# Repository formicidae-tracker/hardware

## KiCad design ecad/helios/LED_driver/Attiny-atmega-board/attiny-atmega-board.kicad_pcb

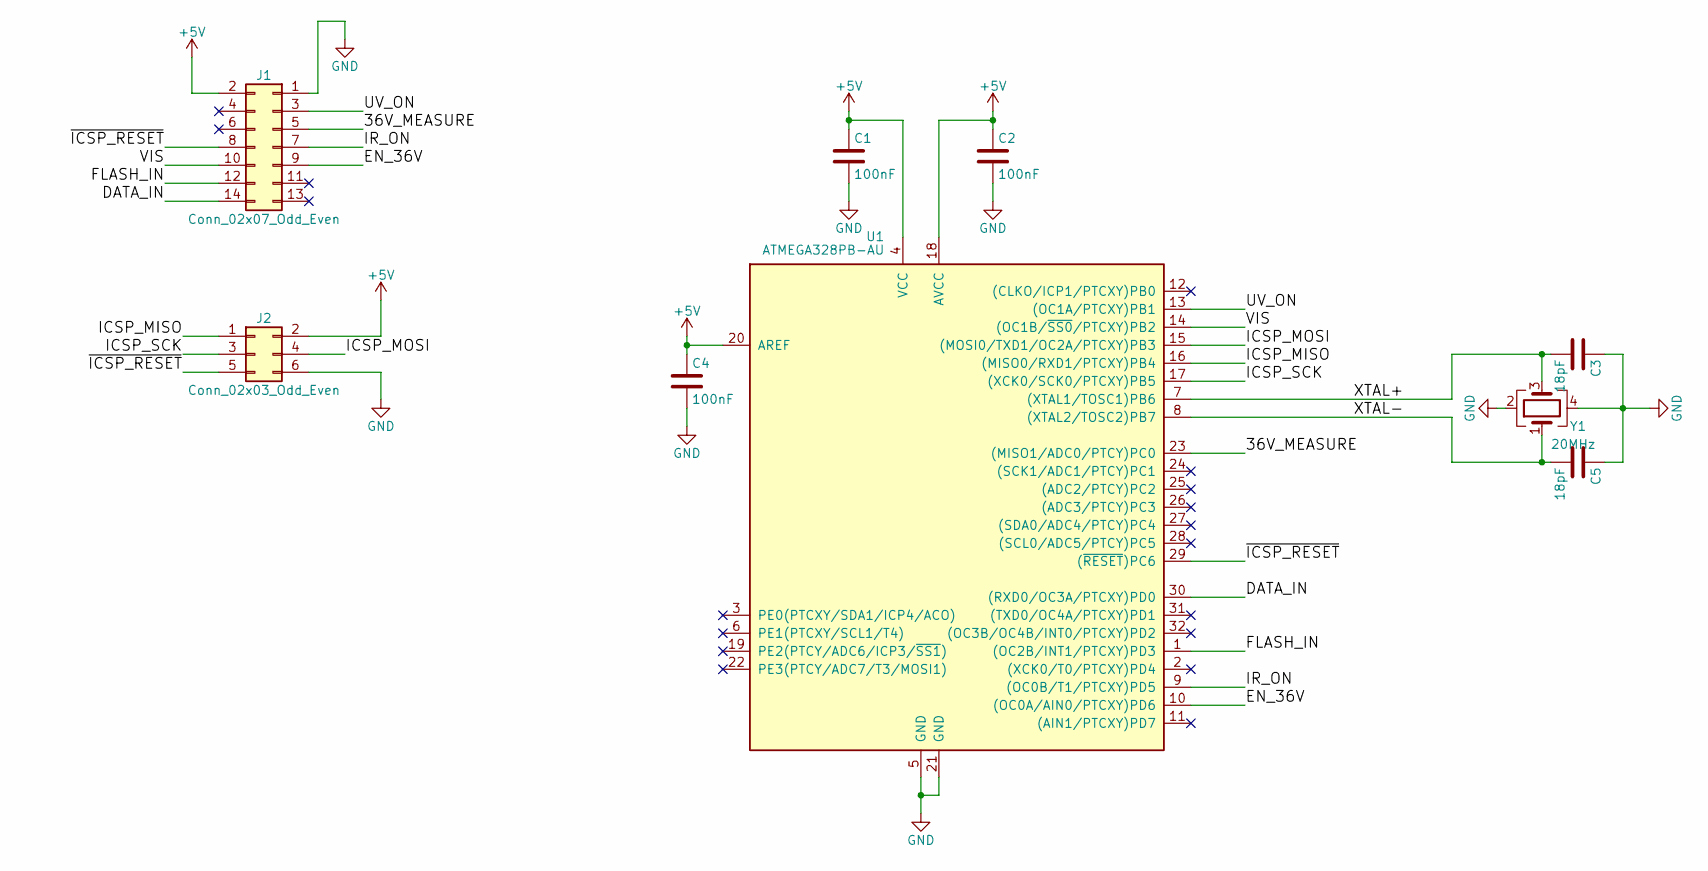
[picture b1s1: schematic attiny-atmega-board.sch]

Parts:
C1, C2, C4: 100nF; C_0603_HandSoldering
C3, C5: 18pF; C_0603_HandSoldering
J1: Conn_02x07_Odd_Even; Pin_Header_Straight_2x07_Pitch1.27mm
J2: Conn_02x03_Odd_Even; Pin_Header_Straight_2x03_Pitch2.54mm_SMD
U1: ATMEGA328PB-AU; TQFP-32_7x7mm_Pitch0.8mm
Y1: 20MHz; Crystal_SMD_Abracon_ABM8G-4pin_3.2x2.5mm; Part Number ABM8G-20.000MHZ-18-D2Y-T

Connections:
+5V: C1.1, C2.1, C4.1, J1.2, J2.2, U1.4 (VCC), U1.18 (AVCC), U1.20 (AREF)
/36V_MEASURE: J1.5, U1.23 ((MISO1/ADC0/PTCY)PC0)
/DATA_IN: J1.14, U1.30 ((RXD0/OC3A/PTCXY)PD0)
/EN_36V: J1.9, U1.10 ((OC0A/AIN0/PTCXY)PD6)
/FLASH_IN: J1.12, U1.1 ((OC2B/INT1/PTCXY)PD3)
/ICSP_MISO: J2.1, U1.16 ((MISO0/RXD1/PTCXY)PB4)
/ICSP_MOSI: J2.4, U1.15 ((MOSI0/TXD1/OC2A/PTCXY)PB3)
/ICSP_SCK: J2.3, U1.17 ((XCK0/SCK0/PTCXY)PB5)
/IR_ON: J1.7, U1.9 ((OC0B/T1/PTCXY)PD5)
/UV_ON: J1.3, U1.13 ((OC1A/PTCXY)PB1)
/VIS: J1.10, U1.14 ((OC1B/~SS0~/PTCXY)PB2)
/XTAL+: C3.2, U1.7 ((XTAL1/TOSC1)PB6), Y1.3
/XTAL-: C5.2, U1.8 ((XTAL2/TOSC2)PB7), Y1.1
/~ICSP_RESET: J1.8, J2.5, U1.29 ((~RESET~)PC6)
GND: C1.2, C2.2, C3.1, C4.2, C5.1, J1.1, J2.6, U1.5 (GND), U1.21 (GND), Y1.2, Y1.4

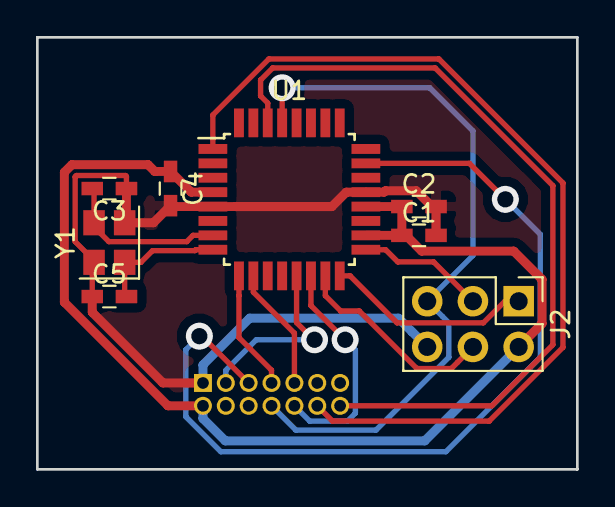
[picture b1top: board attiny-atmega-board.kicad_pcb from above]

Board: 2 copper layers, 30.0 x 24.0 mm, 9 parts (1 on the bottom side), 15 nets.

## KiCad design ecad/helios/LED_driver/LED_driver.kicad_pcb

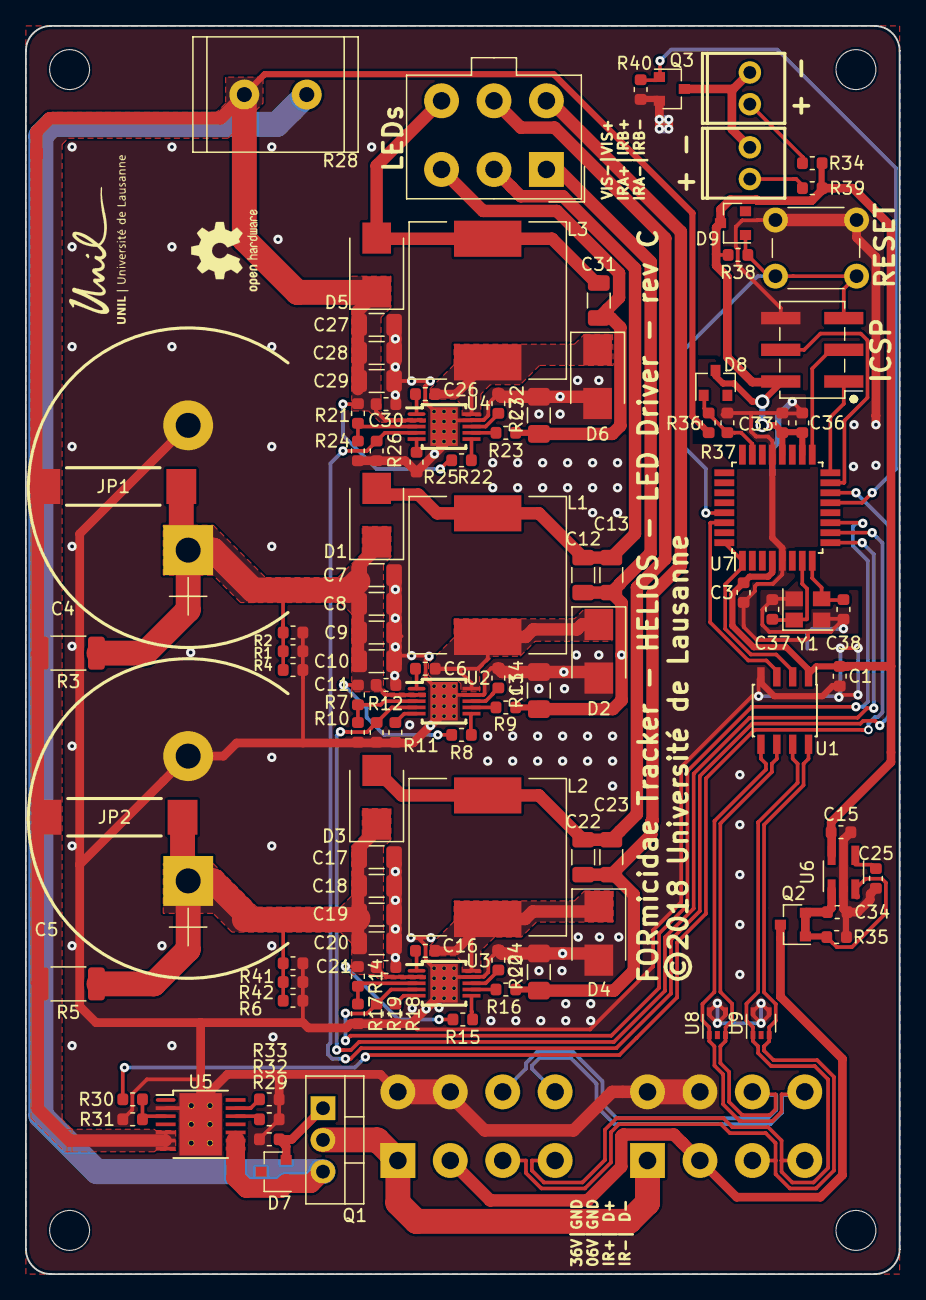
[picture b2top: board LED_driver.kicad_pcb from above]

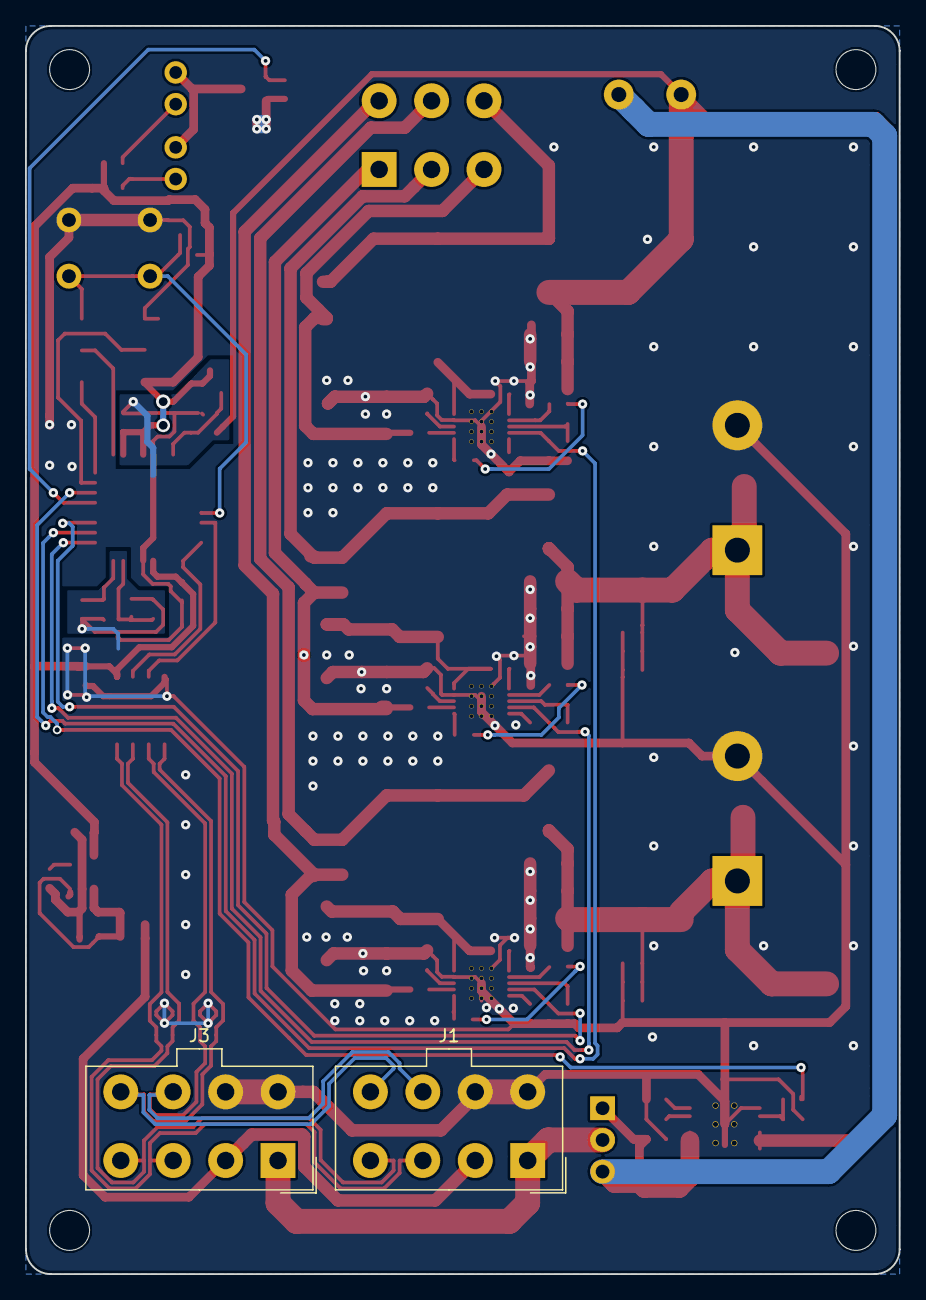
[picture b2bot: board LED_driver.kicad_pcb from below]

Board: 2 copper layers, 70.0 x 100.0 mm, 112 parts (2 on the bottom side), 62 nets.

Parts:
C1, C3, C6, C14, C16, C24, C26, C32, C33, C36: 100nF; C_0603_1608Metric
C4, C5: 4.7mF; CP_Radial_D25.0mm_P10.00mm_SnapIn
C7, C8, C9, C10, C12, C13, C17, C18, C19, C20, C22, C23, C27, C28, C29, C31: 4.7uF,50V; C_1206_3216Metric
C11, C21, C25, C30: 10nF, 50V; C_0603_1608Metric
C15, C34: 1uF; C_0603_1608Metric
C37, C38: 18pF; C_0603_1608Metric
D1, D2, D3, D4, D5, D6: 60V, 2A; D_SMB
D7: 10V; D_SOT-23_KAN
D8, D9: BAT54; D_SOT-23_ANK
J1, J3: 5566-08A2; Molex_MiniFit-JR-5556-08A_2x04x4.20mm_Straight
J2: 5566-06A2; Molex_MiniFit-JR-5556-06A_2x03x4.20mm_Straight
J4: .100 2row header; PinHeader_2x03_P2.54mm_Vertical_SMD
J5, J6: LED HDR; 640454-2
JP1, JP2: S1621-46R
L1, L2, L3: 100uH, 2.5A; 7447709101
Q1: IRF9Z34NPbF; TO-220-3_Vertical
Q2: PMV48XP,215; SOT-23
Q3: BSS138L; SOT-23
R1, R2, R4, R6, R41, R42: 100k; R_0603_1608Metric
R3, R5: 4.7, 3/4W; R_2010_5025Metric
R7, R14, R21: 1.96M; R_0603_1608Metric
R8, R15, R22: 10M; R_0603_1608Metric
R9, R16, R23: 1K; R_0603_1608Metric
R10, R17, R24: 66.5k; R_0603_1608Metric
R11, R18: 267k; R_0603_1608Metric
R12, R19, R26, R29, R31, R32, R35, R36, R40: 100K; R_0603_1608Metric
R13, R20: 0.2, 1%, 0.5W; R_1206_3216Metric_Pad1.42x1.75mm_HandSolder
R25: 162k; R_0603_1608Metric
R27: 3.3, 1%, 0.5W; R_1206_3216Metric_Pad1.42x1.75mm_HandSolder
R28: 47, 5W; R_Radial_Power_L13.0mm_W9.0mm_P5.00mm
R30, R38: 10K; R_0603_1608Metric
R33: 2.94K; R_0603_1608Metric
R34, R39: 82; R_0603_1608Metric
R37: 12.7k; R_0603_1608Metric
SW1: SW_Push; SW_PUSH_6mm
U1: UA9637; SOIC-8_3.9x4.9mm_P1.27mm
U2, U3, U4: TPS92512; PDSO-10-1EP-3x3mm-Pitch0.5mm
U5: TPS1H100AQPWPRQ1; HTSSOP-14-1EP_4.4x6.5mm_Pitch0.65mm_ThermalPad
U6: LP3985IM5-5.0/NOPB; SOT-23-5_HandSoldering
U7: ATMEGA328PB-AU; TQFP-32_7x7mm_P0.8mm
U8, U9: SP1002-02JTG; SOT-353_SC-70-5
Y1: 20MHz; Crystal_SMD_Abracon_ABM8G-4Pin_3.2x2.5mm

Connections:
+5V: C1.2, C3.1, C15.1, C33.1, C36.1, D8.1, D9.1, J4.2, R34.2, R38.1, R39.2, U1.1, U6.5, U7.4, U7.18, U7.20
+36V: C27.1, C28.1, C29.1, C30.1, D5.1, JP1.2, JP2.2, R3.2, R5.2, R21.1, R22.2, R28.2, R36.1, U4.2, U5.5, U5.6, U5.7
/Controller/FLASH_IN: U1.2, U7.1, U7.32
/Controller/ICSP_MISO: J4.1, U7.16
/Controller/ICSP_MOSI: J4.4, U7.15
/Controller/ICSP_SCK: J4.3, U7.17
/Controller/IR_A_ON: R12.1, U2.4, U7.9
/Controller/IR_B_ON: R19.1, U3.4, U7.11
/Controller/UV_ON: Q3.1, R40.1, U7.13
/Controller/V36_MEASURE: D8.2, R36.2, R37.1, U7.23
/Controller/XTAL+: C37.2, U7.7, Y1.1
/Controller/XTAL-: C38.2, U7.8, Y1.3
/Controller/~ICSP_RESET: D9.2, J4.5, R38.2, SW1.2, U7.29
/DATA_+: J1.7, J3.7, U1.6, U8.3
/DATA_-: J1.8, J3.8, U1.5, U8.1
/IRA+: C12.1, C13.1, D1.2, J2.2, L1.2
/IRA-: C12.2, C13.2, J2.1, R9.1, R13.1
/IRB+: C22.1, C23.1, D3.2, J2.5, L2.2
/IRB-: C22.2, C23.2, J2.4, R16.1, R20.1
/LED Drivers/Buck Current Regulator 1.5A 1/PHI: C6.1, D2.1, L1.1, U2.10
/LED Drivers/Buck Current Regulator 1.5A 1/VIN: C4.1, C7.1, C8.1, C9.1, C10.1, C11.1, D1.1, JP1.1, R1.1, R2.1, R3.1, R4.1, R7.1, R8.2, U2.2
/LED Drivers/Buck Current Regulator 1.5A 2/PHI: C16.1, D4.1, L2.1, U3.10
/LED Drivers/Buck Current Regulator 1.5A 2/VIN: C5.1, C17.1, C18.1, C19.1, C20.1, C21.1, D3.1, JP2.1, R5.1, R6.1, R14.1, R15.2, R41.1, R42.1, U3.2
/LED Drivers/Buck Current Regulator 1A/PHI: C26.1, D6.1, L3.1, U4.10
/LED Drivers/VIS_ON: R26.1, U4.4, U7.14
/Power_Management/EN36: R30.2, U7.10
/Power_Management/V6_PROTECTED: C34.1, Q2.1, Q2.2, R35.1, U6.1, U6.3
/Power_Management/V36_PROTECTED: D7.1, Q1.3, R28.1, U5.8, U5.9, U5.10
/Receivers/DATA: U1.3, U7.30
/TRIG_+: J1.3, J3.3, U1.8, U9.3
/TRIG_-: J1.4, J3.4, U1.7, U9.1
/VIS+: C31.1, D5.2, J2.6, L3.2
/VIS-: C31.2, J2.3, R23.1, R27.1
/VS6: J1.2, J3.2, Q2.3
/VS36: J1.1, J3.1, Q1.2
GND: C1.1, C3.2, C4.2, C5.2, C7.2, C8.2, C9.2, C10.2, C11.2, C14.2, C15.2, C17.2, C18.2, C19.2, C20.2, C21.2, C24.2, C25.2, C27.2, C28.2, C29.2, C30.2, C32.2, C33.2, C34.2, C36.2, C37.1, C38.1, D2.2, D4.2, D6.2, J1.5, J1.6, J3.5, J3.6, J4.6, Q3.2, R1.2, R2.2, R4.2, R6.2, R10.2, R11.2, R12.2, R13.2, R17.2, R18.2, R19.2, R20.2, R24.2, R25.2, R26.2, R27.2, R29.2, R31.2, R32.2, R33.2, R35.2, R37.2, R40.2, R41.2, R42.2, SW1.1, U1.4, U2.9, U2.11, U3.9, U3.11, U4.9, U4.11, U5.2, U5.15, U6.2, U7.5, U7.21, U8.4, U8.5, U9.4, U9.5, Y1.2, Y1.4
unnamed: C6.2, U2.1
unnamed: C14.1, U2.8
unnamed: C16.2, U3.1
unnamed: C24.1, U3.8
unnamed: C25.1, U6.4
unnamed: C26.2, U4.1
unnamed: C32.1, U4.8
unnamed: D7.2, Q1.1, R29.1
unnamed: J5.1, R34.1
unnamed: J5.2, J6.2, Q3.3
unnamed: J6.1, R39.1
unnamed: R8.1, U2.6
unnamed: R9.2, U2.7
unnamed: R7.2, R10.1, U2.3
unnamed: R11.1, U2.5
unnamed: R14.2, R17.1, U3.3
unnamed: R15.1, U3.6
unnamed: R16.2, U3.7
unnamed: R18.1, U3.5
unnamed: R21.2, R24.1, U4.3
unnamed: R22.1, U4.6
unnamed: R23.2, U4.7
unnamed: R25.1, U4.5
unnamed: R30.1, R31.1, U5.3
unnamed: R32.1, U5.12
unnamed: R33.1, U5.13

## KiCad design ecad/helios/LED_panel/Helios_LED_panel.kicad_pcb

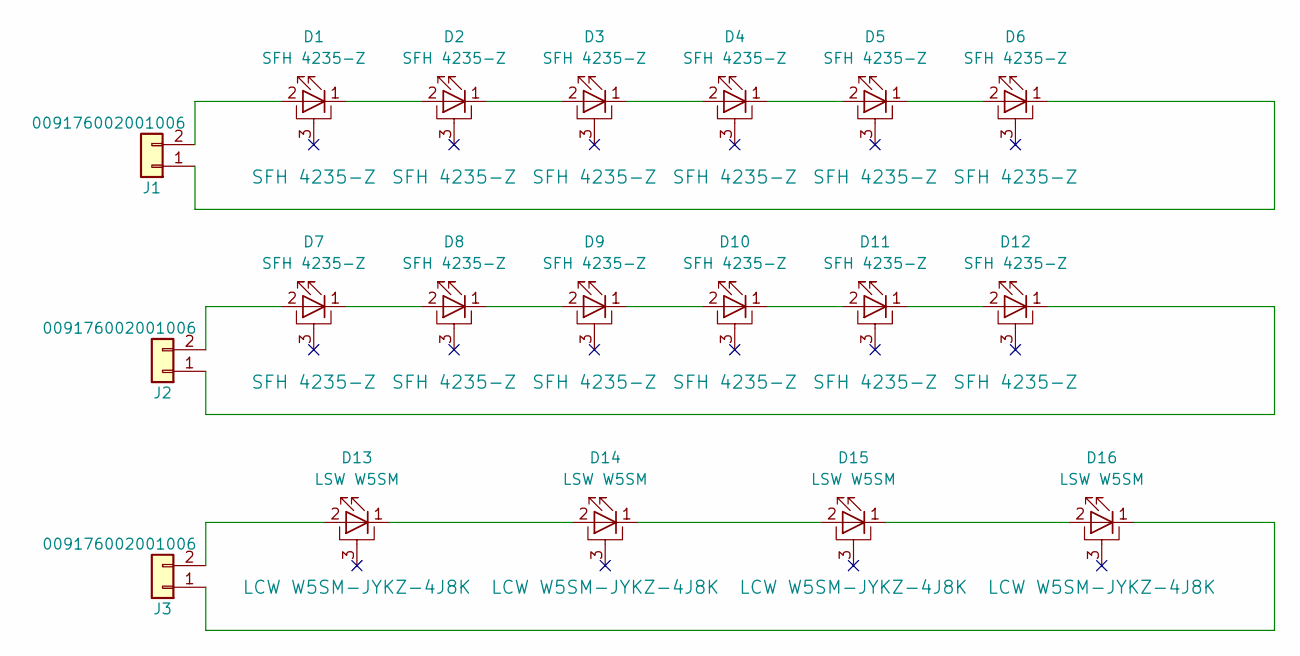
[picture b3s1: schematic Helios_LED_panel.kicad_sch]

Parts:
D1, D2, D3, D4, D5, D6, D7, D8, D9, D10, D11, D12: SFH 4235-Z; OSRAM_Platinium_Dragon
D13, D14, D15, D16: LSW W5SM; OSRAM_Platinium_Dragon
J1, J2, J3: 009176002001006; 009176002701106

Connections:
unnamed: D1.1 (K), D2.2 (A)
unnamed: D1.2 (A), J1.2
unnamed: D2.1 (K), D3.2 (A)
unnamed: D3.1 (K), D4.2 (A)
unnamed: D4.1 (K), D5.2 (A)
unnamed: D5.1 (K), D6.2 (A)
unnamed: D6.1 (K), J1.1
unnamed: D7.1 (K), D8.2 (A)
unnamed: D7.2 (A), J2.2
unnamed: D8.1 (K), D9.2 (A)
unnamed: D10.1 (K), D11.2 (A)
unnamed: D9.1 (K), D10.2 (A)
unnamed: D11.1 (K), D12.2 (A)
unnamed: D12.1 (K), J2.1
unnamed: D13.1 (K), D14.2 (A)
unnamed: D13.2 (A), J3.2
unnamed: D14.1 (K), D15.2 (A)
unnamed: D15.1 (K), D16.2 (A)
unnamed: D16.1 (K), J3.1

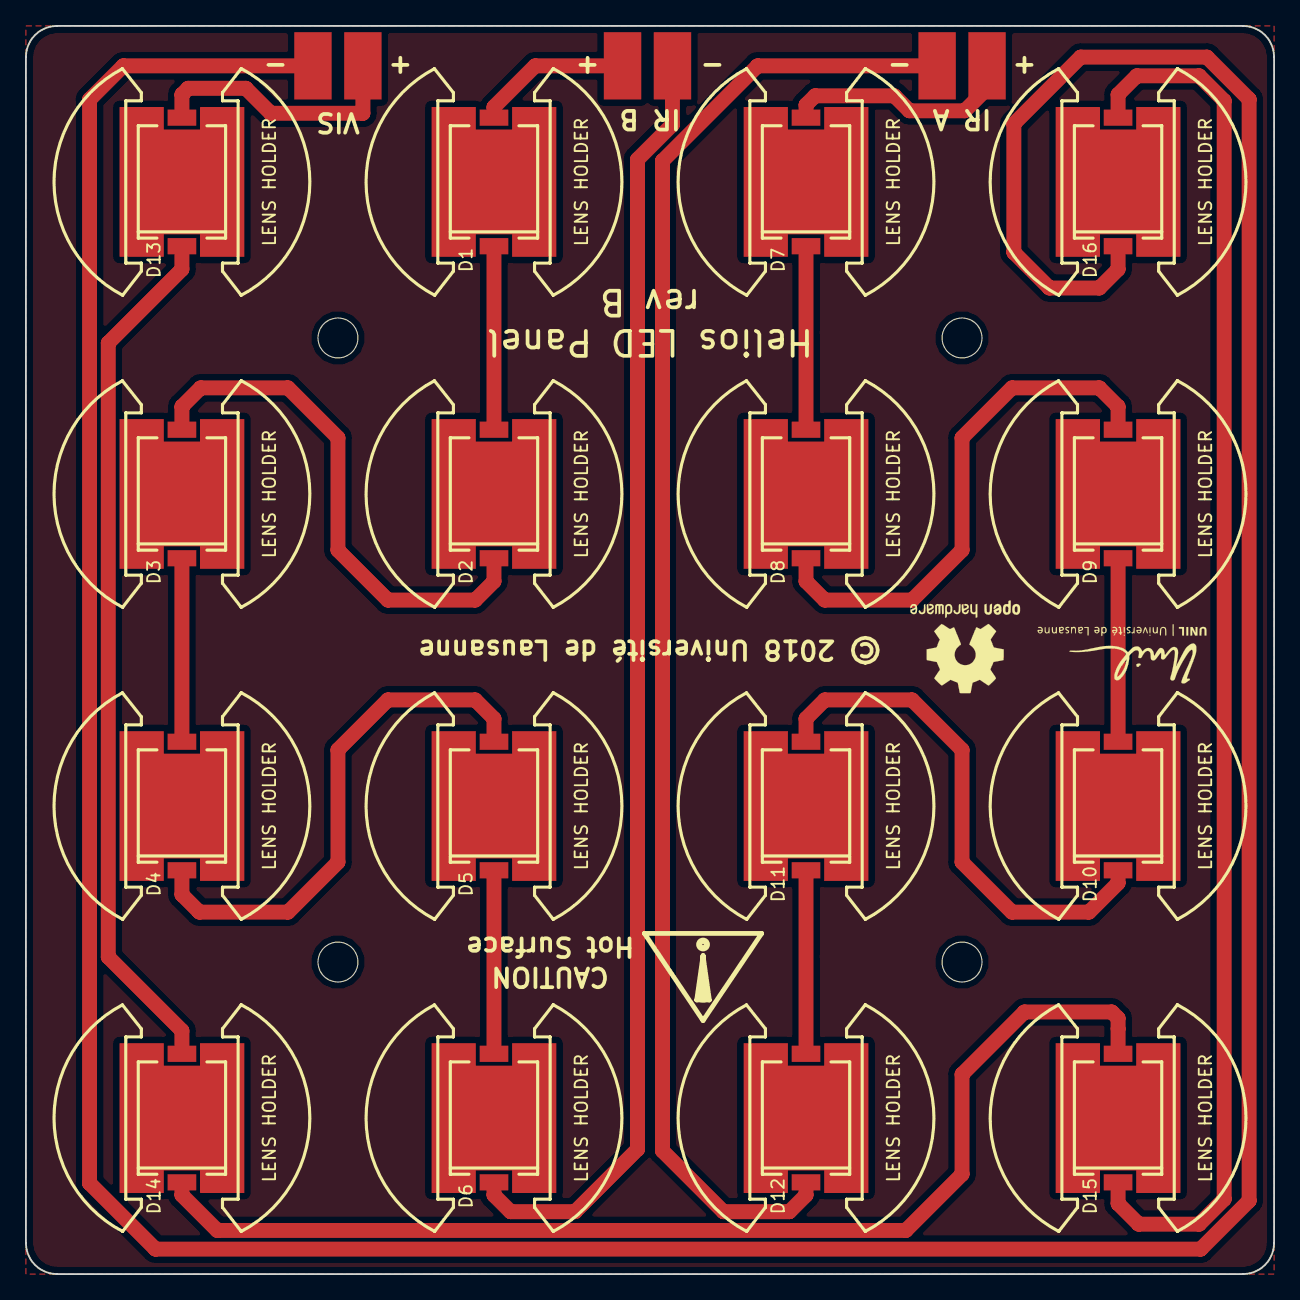
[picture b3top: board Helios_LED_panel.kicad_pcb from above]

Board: 2 copper layers, 100.0 x 100.0 mm, 19 parts (0 on the bottom side), 19 nets.

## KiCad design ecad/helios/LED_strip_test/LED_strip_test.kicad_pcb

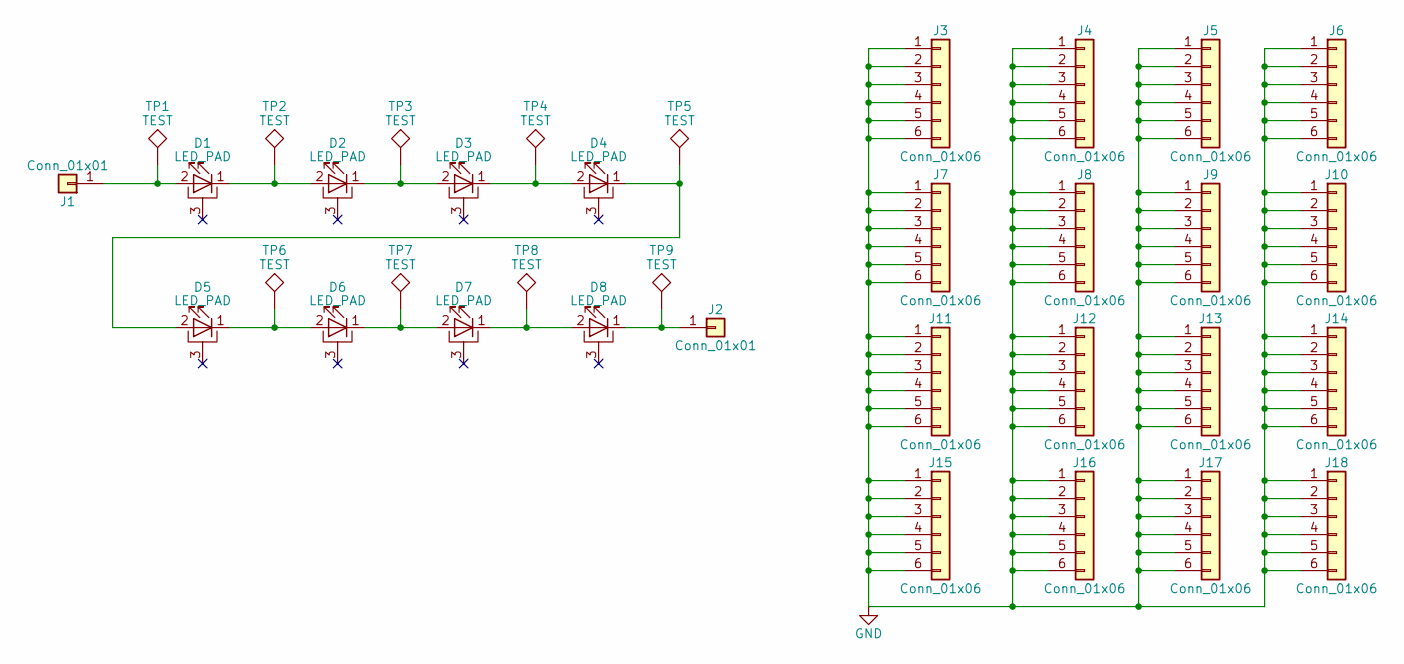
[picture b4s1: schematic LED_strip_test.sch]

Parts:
D1, D2, D3, D4, D5, D6, D7, D8: LED_PAD; OSRAM_Platinium_Dragon
J1, J2: Conn_01x01; SolderWirePad_single_1-5mmDrill
J3, J4, J5, J6, J7, J8, J9, J10, J11, J12, J13, J14, J15, J16, J17, J18: Conn_01x06; Pin_Header_Straight_1x06_Pitch2.54mm_Centered
TP1, TP2, TP3, TP4, TP5, TP6, TP7, TP8, TP9: TEST; SolderWirePad_single_1-5mmDrill

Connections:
GND: J3.1, J3.2, J3.3, J3.4, J3.5, J3.6, J4.1, J4.2, J4.3, J4.4, J4.5, J4.6, J5.1, J5.2, J5.3, J5.4, J5.5, J5.6, J6.1, J6.2, J6.3, J6.4, J6.5, J6.6, J7.1, J7.2, J7.3, J7.4, J7.5, J7.6, J8.1, J8.2, J8.3, J8.4, J8.5, J8.6, J9.1, J9.2, J9.3, J9.4, J9.5, J9.6, J10.1, J10.2, J10.3, J10.4, J10.5, J10.6, J11.1, J11.2, J11.3, J11.4, J11.5, J11.6, J12.1, J12.2, J12.3, J12.4, J12.5, J12.6, J13.1, J13.2, J13.3, J13.4, J13.5, J13.6, J14.1, J14.2, J14.3, J14.4, J14.5, J14.6, J15.1, J15.2, J15.3, J15.4, J15.5, J15.6, J16.1, J16.2, J16.3, J16.4, J16.5, J16.6, J17.1, J17.2, J17.3, J17.4, J17.5, J17.6, J18.1, J18.2, J18.3, J18.4, J18.5, J18.6
unnamed: D1.1 (K), D2.2 (A), TP2.1
unnamed: D1.2 (A), J1.1, TP1.1
unnamed: D2.1 (K), D3.2 (A), TP3.1
unnamed: D3.1 (K), D4.2 (A), TP4.1
unnamed: D4.1 (K), D5.2 (A), TP5.1
unnamed: D5.1 (K), D6.2 (A), TP6.1
unnamed: D6.1 (K), D7.2 (A), TP7.1
unnamed: D7.1 (K), D8.2 (A), TP8.1
unnamed: D8.1 (K), J2.1, TP9.1

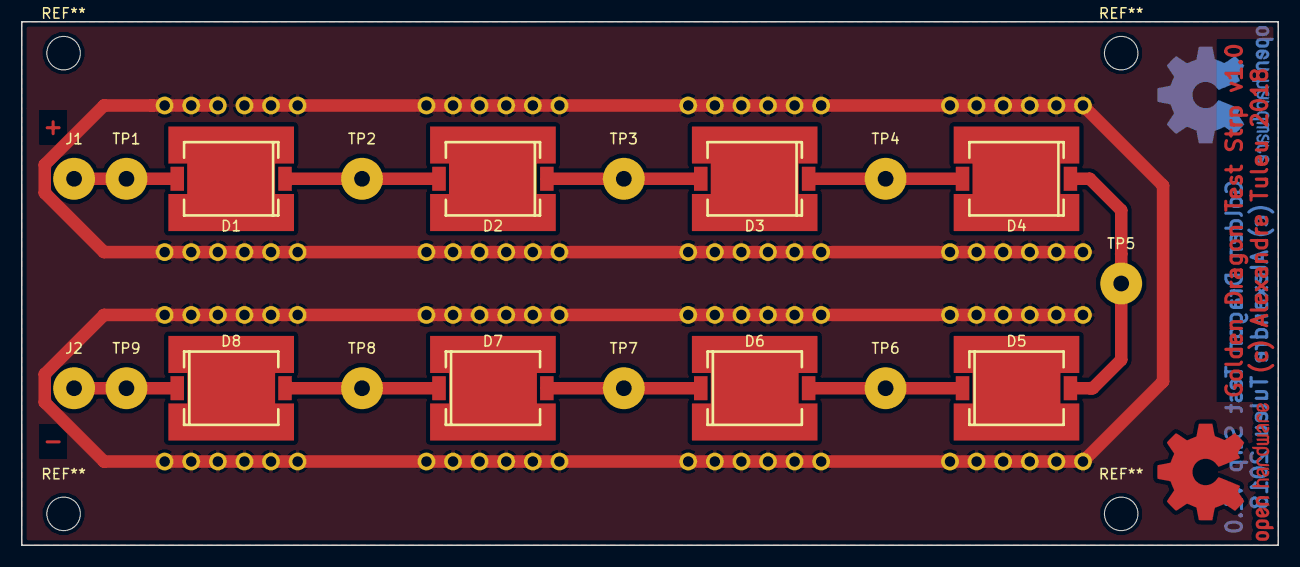
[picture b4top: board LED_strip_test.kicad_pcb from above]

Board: 2 copper layers, 120.0 x 50.0 mm, 35 parts (0 on the bottom side), 10 nets.

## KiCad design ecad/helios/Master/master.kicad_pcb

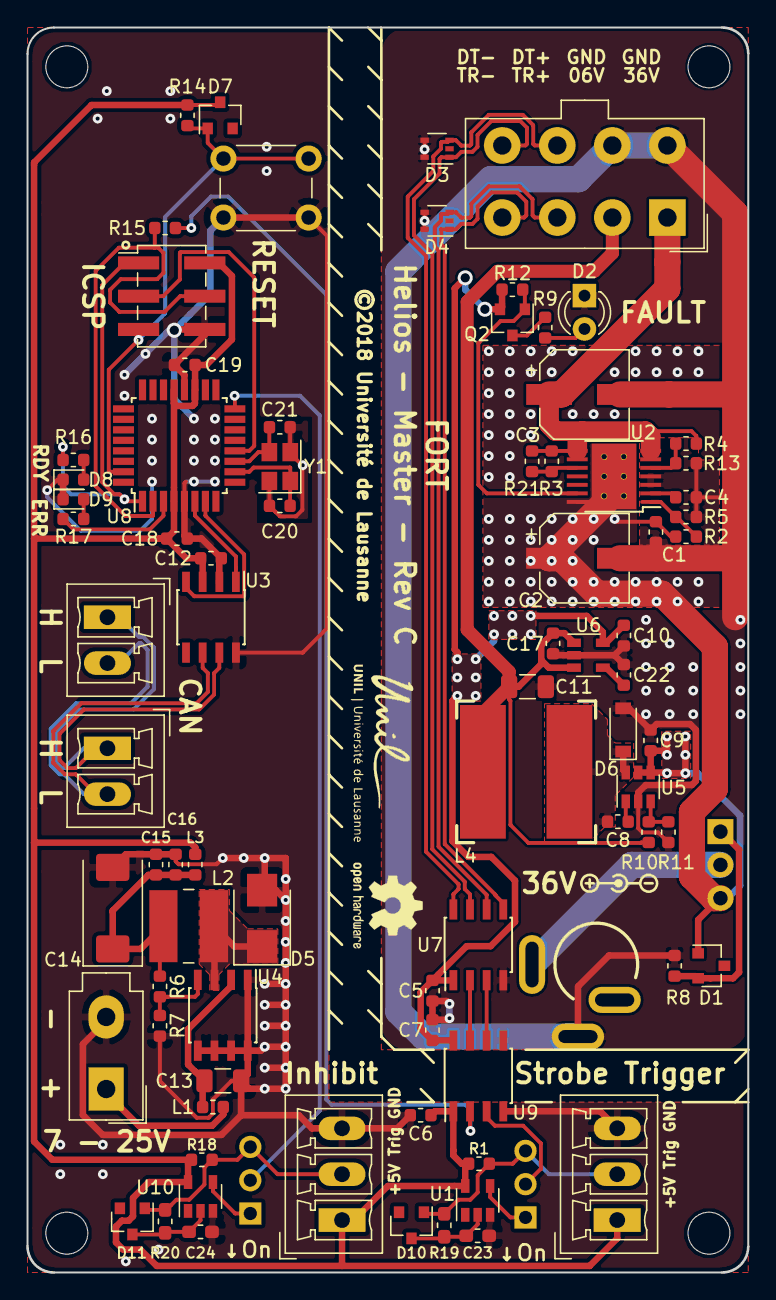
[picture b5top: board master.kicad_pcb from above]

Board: 2 copper layers, 55.0 x 95.0 mm, 88 parts (1 on the bottom side), 53 nets.

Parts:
C1, C5, C6, C7, C12, C16, C18, C19: 100n; C_0603_1608Metric
C2, C3: 47uF; CP_Elec_6.3x7.7
C4, C22: 10nF, 50V; C_0603_1608Metric
C8: 0.22uF, 25V; C_0603_1608Metric
C9, C10, C17: 1uF, 50V; C_0603_1608Metric
C11: 47uF, 10V; C_1206_3216Metric
C13: 22uF, 25V; C_1206_3216Metric
C14: 470u, 6.3V; CP_EIA-7343-31_Kemet-D
C15: 4u7, 6.3V; C_0603_1608Metric
C20, C21: 18pF; C_0603_1608Metric
C23, C24: 1nF; C_0603_1608Metric_Pad1.05x0.95mm_HandSolder
D1: 10V; D_SOT-23_KAN
D2: RED; LED_D3.0mm
D3, D4: SP1002-02TG; SOT-353_SC-70-5
D5: B260, 60V, 2A; D_SMB
D6: 60V, 1A; D_SOD-123
D7, D10, D11: BAT54; D_SOT-23_ANK
D8: GREEN; LED_0603_1608Metric
D9: YELLOW; LED_0603_1608Metric
J1: 5566-02A; Molex_Mini-Fit_Jr_5566-02A_2x01_P4.20mm_Vertical
J2, J3: MCV 1,5/ 2-G-3,5; PhoenixContact_MCV_1,5_2-G-3.5_1x02_P3.50mm_Vertical
J4, J8: MCV 1,5/ 3-G-3,5; PhoenixContact_MCV_1,5_3-G-3.5_1x03_P3.50mm_Vertical
J5: PJ-032A
J6: MiniFit JR 5566 08A2; Molex_MiniFit-JR-5556-08A_2x04x4.20mm_Straight
J7: M20-8760342; PinHeader_2x03_P2.54mm_Vertical_SMD
JP1, JP2: .100 Header; PinHeader_1x03_P2.54mm_Vertical
L1, L3: 500mA Fuse; R_0603_1608Metric
L2: 68uH, 560mA; L_Wuerth_WE-PD2-Typ-MS
L4: 100uH, 0.7A; SRN1060-XXXM
MH1, MH2, MH3, MH4: M3; MountingHole_3.2mm_M3_DIN965
Q1: IRF9Z34NPbF; TO-220-3_Horizontal_TabDown
Q2: BSS84P; SOT-23
R1, R5, R13, R14, R18: 10K; R_0603_1608Metric
R2: 270k; R_0603_1608Metric
R3, R21: 51; R_0603_1608Metric
R4: 390k; R_0603_1608Metric
R6: 15k; R_0603_1608Metric
R7: 4k87; R_0603_1608Metric
R8, R12: 100K; R_0603_1608Metric
R9, R11, R16, R17: 1k; R_0603_1608Metric
R10: 6.98K; R_0603_1608Metric
R15: 1K; R_0603_1608Metric
R19, R20: 10K; R_0603_1608Metric_Pad1.05x0.95mm_HandSolder
SW1: 1825910-6; SW_PUSH_6mm
U1, U10: 74LVC1G17; SOT-23-5
U2: STEF01FTR; HTSSOP-14-1EP_4.4x6.5mm_Pitch0.65mm_ThermalPad
U3: MCP2561-E/SN; SOIC-8_3.9x4.9mm_P1.27mm
U4: MIC4680YM; SOIC-8_3.9x4.9mm_P1.27mm
U5: LM2842Y; SOT-23-6
U6: LP3985IM5-5.0/NOPB; SOT-23-5
U7: UA9638; SOIC-8_3.9x4.9mm_P1.27mm
U8: ATMEGA16M1-AU; TQFP-32_7x7mm_P0.8mm
U9: ISO7320FC; SOIC-8_3.9x4.9mm_P1.27mm
Y1: 16MHz; Crystal_SMD_SeikoEpson_FA238-4Pin_3.2x2.5mm

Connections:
+5V: C6.1, C12.1, C18.1, C19.1, D7.1, J4.1, J7.2, J8.1, L3.1, R1.1, R14.1, R18.1, U1.5, U3.3, U8.4, U8.19, U8.21, U9.1, U10.5
+12V: J1.1, L1.2
/12V to 5V LDO/5V_UNPROTECTED: C14.1, C15.1, C16.1, L2.2, L3.2, R6.1
/12V to 5V LDO/FB: R6.2, R7.1, U4.4
/12V to 5V LDO/SW: D5.1, L2.1, U4.3
/12V to 5V LDO/VIN_PROTECTED: C13.1, L1.1, U4.2
/CAN Transceiver/CAN+: J2.1, J3.1, U3.7
/CAN Transceiver/CAN-: J2.2, J3.2, U3.6
/Filter 1/FILTERED: JP1.1, U1.4
/Filter 1/IN: D10.2, J4.2, JP1.3, R1.2, R19.2
/Filter 1/SMOOTHED: C23.1, D10.1, R19.1, U1.2
/Filter 2/FILTERED: JP2.1, U10.4
/Filter 2/IN: D11.2, J8.2, JP2.3, R18.2, R20.2
/Filter 2/SMOOTHED: C24.1, D11.1, R20.1, U10.2
/INHIBIT: JP2.2, U8.16
/Output/6V_Regulator/BOOT: C8.1, U5.1
/Output/6V_Regulator/BYPASS: C22.1, U6.4
/Output/6V_Regulator/FB: R10.2, R11.1, U5.3
/Output/6V_Regulator/SW: C8.2, D6.1, L4.1, U5.6
/Output/DATA: R15.1, U9.2
/Output/DATA_+: D3.3, J6.7, U7.8
/Output/DATA_-: D3.1, J6.8, U7.7
/Output/DATA_ISO: U7.2, U9.7
/Output/GNDSUPPLY: C1.2, C2.2, C3.2, C4.2, C5.2, C7.2, C9.2, C10.2, C11.2, C17.2, C22.2, D2.1, D3.4, D3.5, D4.4, D4.5, D6.2, J5.2, J6.5, J6.6, R5.2, R8.2, R11.2, R13.2, U2.3, U2.4, U5.2, U6.2, U7.4, U9.5
/Output/ILIM: R3.2, R21.2, U2.10
/Output/IR_ON+: D4.3, J6.3, U7.6
/Output/IR_ON-: D4.1, J6.4, U7.5
/Output/LED_LIM: D2.2, R9.2
/Output/LED_ON: Q2.3, R9.1
/Output/PG: Q2.1, R12.2, U2.13
/Output/REV_ON: D1.2, Q1.1, R8.1
/Output/TRIGGER_ISO: U7.3, U9.6
/Output/UVLO: R2.2, R5.1, U2.1
/Output/V5: C5.1, C7.1, C10.1, Q2.2, R12.1, U6.5, U7.1, U9.8
/Output/V6: C11.1, C17.1, J6.2, L4.2, R10.1, U6.1, U6.3
/Output/V36: C3.1, J6.1, R3.1, R4.1, R21.1, U2.6, U2.7, U2.8, U2.9
/Output/VCLAMP: R4.2, R13.1, U2.5
/Output/VSUPPLY: J5.1, Q1.2
/Output/V_PROTECTED: C1.1, C2.1, C9.1, D1.1, Q1.3, R2.1, U2.14, U2.15, U5.4, U5.5
/Output/dVdt: C4.1, U2.2
/TRIGGER: JP1.2, U9.3
/UC/ICSP_MISO: J7.1, R16.1, U8.1
/UC/ICSP_MOSI: J7.4, R15.2, U8.2
/UC/ICSP_SCK: J7.3, U8.12
/UC/LED_ERROR: R17.1, U8.3
/UC/RXCAN: U3.4, U8.7
/UC/TXCAN: U3.1, U8.6
/UC/XTAL1: C20.2, U8.10, Y1.1
/UC/XTAL2: C21.2, U8.11, Y1.3
/UC/~ICSP_RESET: D7.2, J7.5, R14.2, SW1.2, U8.31
GND: C6.2, C12.2, C13.2, C14.2, C15.2, C16.2, C18.2, C19.2, C20.1, C21.1, C23.2, C24.2, D5.2, D8.1, D9.1, J1.2, J4.3, J7.6, J8.3, R7.2, SW1.1, U1.3, U3.2, U3.8, U4.1, U4.5, U4.6, U4.7, U4.8, U8.5, U8.20, U9.4, U10.3, Y1.2, Y1.4
unnamed: D8.2, R16.2
unnamed: D9.2, R17.2

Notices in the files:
ecad/helios/LED_driver/LED_driver.kicad_pcb:
©2018 Université de Lausanne
